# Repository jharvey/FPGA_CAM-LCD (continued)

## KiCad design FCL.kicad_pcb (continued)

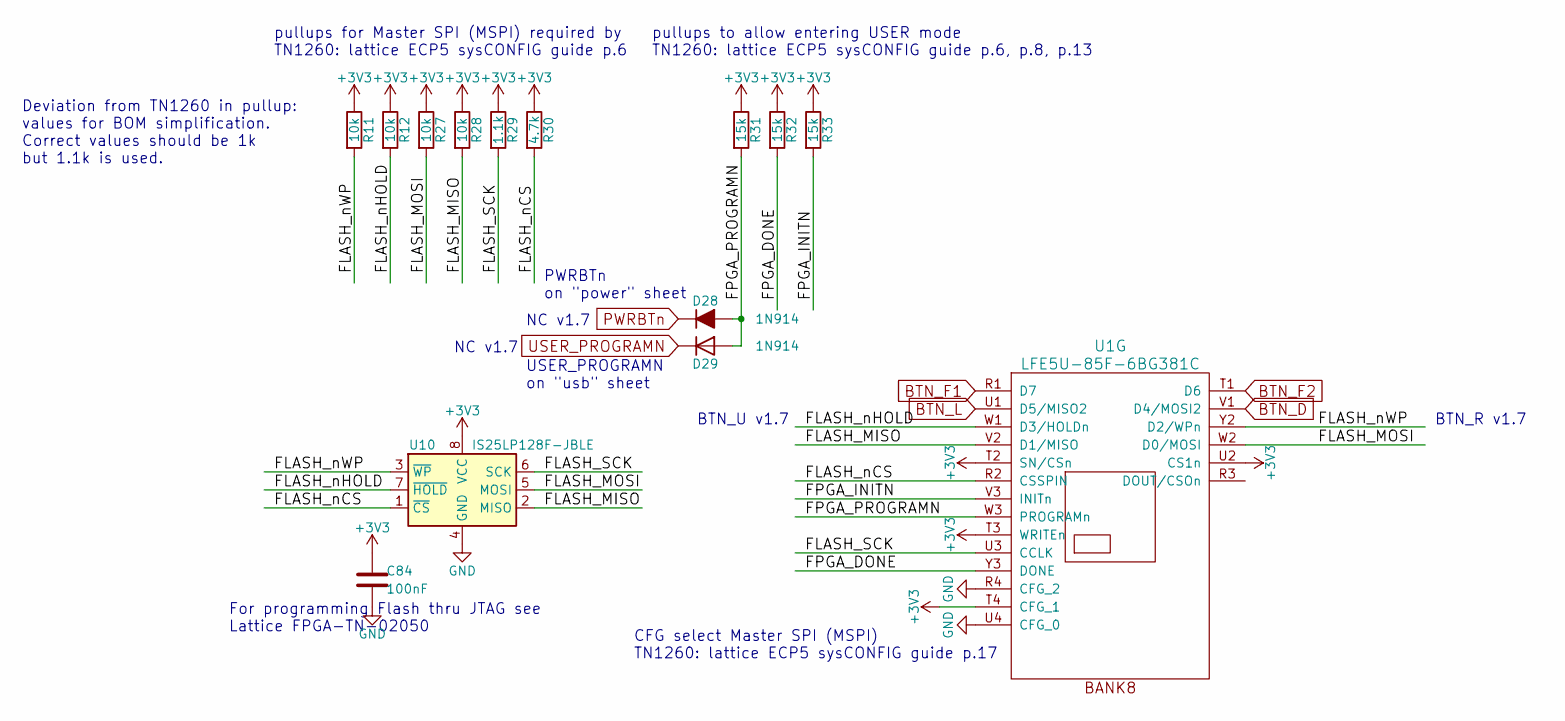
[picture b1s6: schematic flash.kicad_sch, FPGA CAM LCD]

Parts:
C84: 100nF; C_0402_1005Metric; LCSC C1525
D28: 1N914; D_SOD-323_HandSoldering; Digike_y 1N4148WXTPMSCT-ND
D29: 1N914; D_SOD-323_HandSoldering
R11: 10k; R_0603_1608Metric; MPN RC0603FR-0710KL; Mouser 603-RC0603FR-0710KL
R12, R27, R28: 10k; R_0603_1608Metric
R29: 1.1k; R_0603_1608Metric
R30: 4.7k; R_0603_1608Metric; MPN AC0603FR-104K7L
R31, R32, R33: 15k; R_0603_1608Metric
U1: LFE5U-85F-6BG381C; BGA-381_pitch0.8mm_dia0.4mm; MPN LFE5U-85F-6BG381C
U10: IS25LP128F-JBLE; SOA008-150-208mil; MPN IS25LP128F-JBLE; Mouser 454-W25Q128JVSIMTR

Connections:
+3V3: C84.1, R11.1, R12.1, R27.1, R28.1, R29.1, R30.1, R31.1, R32.1, R33.1, U1.T2 (SN/CSn), U1.T3 (WRITEn), U1.T4 (CFG_1), U1.U2 (CS1n), U10.8 (VCC); also elsewhere on the board
/flash/FLASH_MISO: R28.2, U1.V2 (D1/MISO), U10.2 (MISO)
/flash/FLASH_MOSI: R27.2, U1.W2 (D0/MOSI), U10.5 (MOSI)
/flash/FLASH_SCK: R29.2, U1.U3 (CCLK), U10.6 (SCK)
/flash/FLASH_nCS: R30.2, U1.R2 (CSSPIN), U10.1 (~CS)
/flash/FLASH_nHOLD: R12.2, U1.W1 (D3/HOLDn), U10.7 (~HOLD)
/flash/FLASH_nWP: R11.2, U1.Y2 (D2/WPn), U10.3 (~WP)
/flash/FPGA_DONE: R32.2, U1.Y3 (DONE)
/flash/FPGA_INITN: R33.2, U1.V3 (INITn)
/flash/FPGA_PROGRAMN: D28.2 (A), D29.2 (A), R31.2, U1.W3 (PROGRAMn)
BTN_D: U1.V1 (D4/MOSI2)
BTN_F1: U1.R1 (D7)
BTN_F2: U1.T1 (D6)
BTN_L: U1.U1 (D5/MISO2)
GND: C84.2, U1.R4 (CFG_2), U1.U4 (CFG_0), U10.4 (GND); also elsewhere on the board
PWRBTn: D28.1 (K); also elsewhere on the board
USER_PROGRAMN: D29.1 (K); also elsewhere on the board

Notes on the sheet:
CFG select Master SPI (MSPI) TN1260: lattice ECP5 sysCONFIG guide p.17
USER_PROGRAMN on "usb" sheet
NC v1.7
For programming Flash thru JTAG see Lattice FPGA-TN-02050
Deviation from TN1260 in pullup: values for BOM simplification. Correct values should be 1k but 1.1k is used.
BTN_R v1.7
pullups to allow entering USER mode TN1260: lattice ECP5 sysCONFIG guide p.6, p.8, p.13
PWRBTn on "power" sheet
BTN_U v1.7
pullups for Master SPI (MSPI) required by TN1260: lattice ECP5 sysCONFIG guide p.6

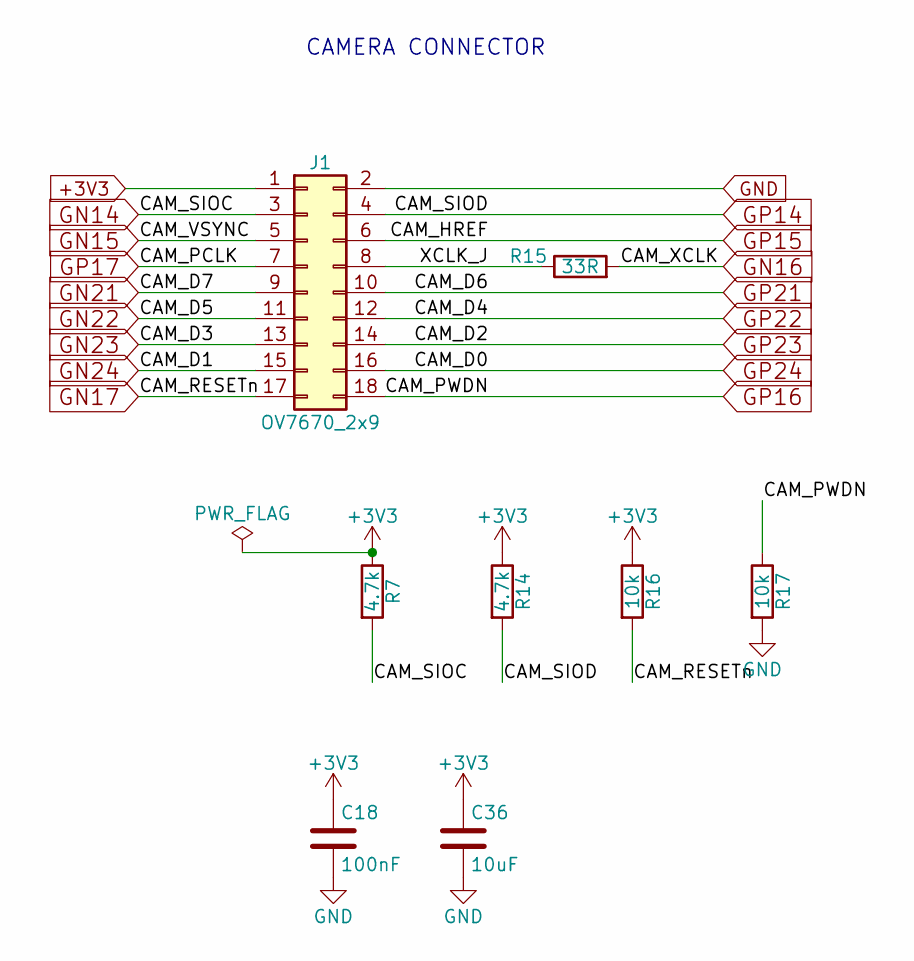
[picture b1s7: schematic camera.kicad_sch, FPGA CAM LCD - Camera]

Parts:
C18: 100nF; C_0402_1005Metric; LCSC C1525
C36: 10uF; C_0805_2012Metric; LCSC C15850
J1: OV7670_2x9; PinSocket_2x09_P2.54mm_Vertical; LCSC C71956
R7, R14: 4.7k; R_0402_1005Metric; LCSC C25900
R15: 33R; R_0402_1005Metric; LCSC C25105
R16, R17: 10k; R_0402_1005Metric; LCSC C25744

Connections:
+3V3: C18.1, C36.1, J1.1, R7.1, R14.1, R16.1; also elsewhere on the board
/camera/XCLK_J: J1.8, R15.1
CAM_XCLK: R15.2; also elsewhere on the board
GN14: J1.3, R7.2; also elsewhere on the board
GN15: J1.5; also elsewhere on the board
GN17: J1.17, R16.2; also elsewhere on the board
GN21: J1.9; also elsewhere on the board
GN22: J1.11; also elsewhere on the board
GN23: J1.13; also elsewhere on the board
GN24: J1.15; also elsewhere on the board
GND: C18.2, C36.2, J1.2, R17.2; also elsewhere on the board
GP14: J1.4, R14.2; also elsewhere on the board
GP15: J1.6; also elsewhere on the board
GP16: J1.18, R17.1; also elsewhere on the board
GP17: J1.7; also elsewhere on the board
GP21: J1.10; also elsewhere on the board
GP22: J1.12; also elsewhere on the board
GP23: J1.14; also elsewhere on the board
GP24: J1.16; also elsewhere on the board

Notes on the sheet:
CAMERA CONNECTOR

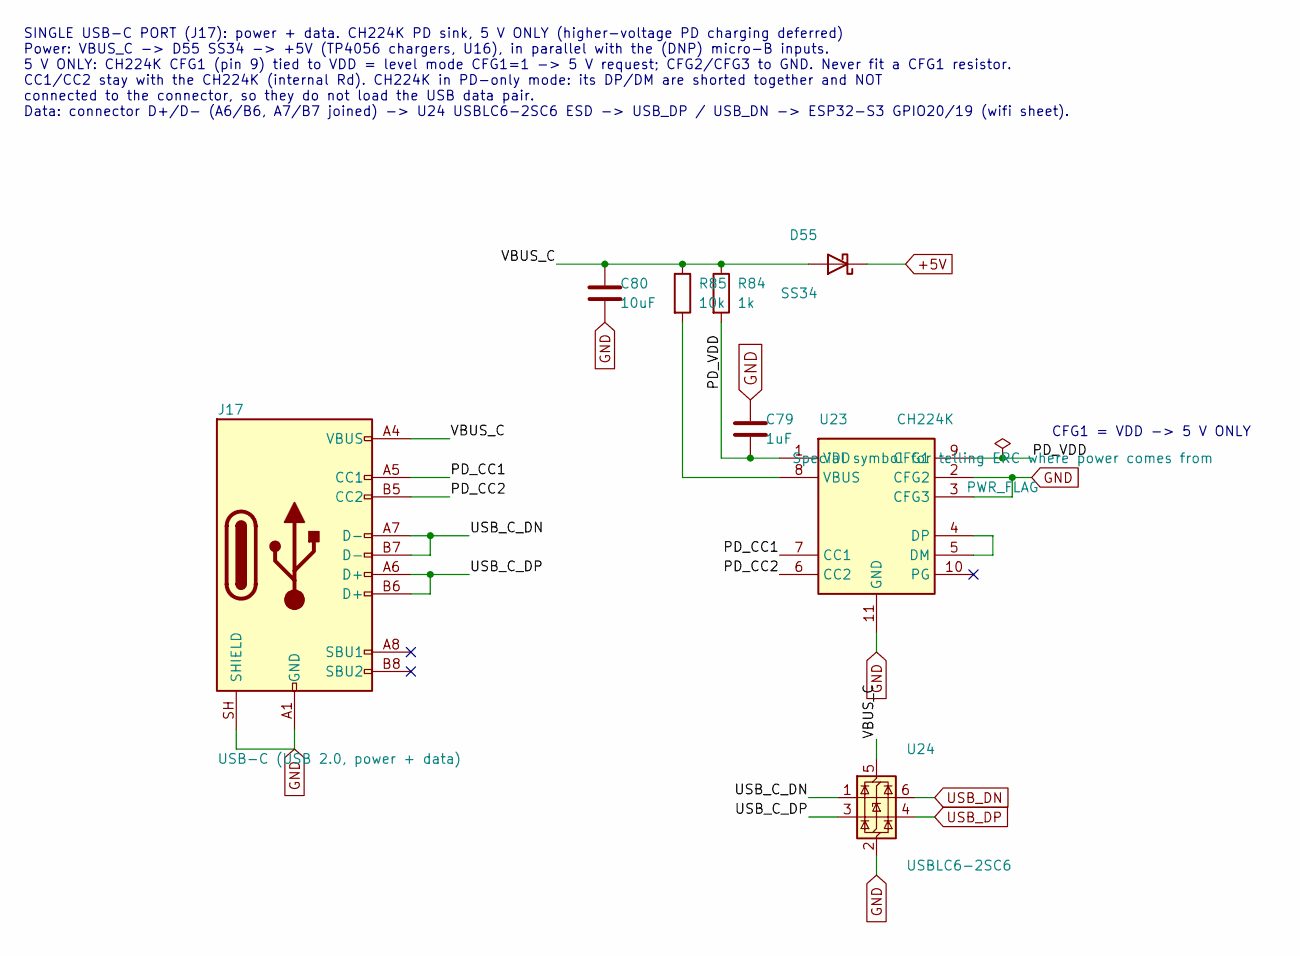
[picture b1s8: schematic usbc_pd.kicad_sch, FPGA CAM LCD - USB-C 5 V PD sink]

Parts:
C79: 1uF; C_0603_1608Metric; LCSC C15849
C80: 10uF; C_0805_2012Metric; LCSC C15850
D55: SS34; D_SMA; MPN SS34; LCSC C8678
J17: USB-C (USB 2.0, power + data); USB_C_Receptacle_HCTL_HC-TYPE-C-16P-01A; MPN HC-TYPE-C-16P-01A; LCSC C2894897
R84: 1k; R_0603_1608Metric; LCSC C21190
R85: 10k; R_0402_1005Metric; LCSC C25744
U23: CH224K; SSOP-10-1EP_3.9x4.9mm_P1mm_EP2.1x3.3mm; MPN CH224K; LCSC C970725
U24: USBLC6-2SC6; SOT-23-6; MPN USBLC6-2SC6; LCSC C7519

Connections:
+5V: D55.1 (K); also elsewhere on the board
/usbc_pd/PD_CC1: J17.A5 (CC1), U23.7 (CC1)
/usbc_pd/PD_CC2: J17.B5 (CC2), U23.6 (CC2)
/usbc_pd/PD_VDD: C79.2, R84.2, U23.1 (VDD), U23.9 (CFG1)
/usbc_pd/USB_C_DN: J17.A7 (D-), J17.B7 (D-), U24.1 (I/O1)
/usbc_pd/USB_C_DP: J17.A6 (D+), J17.B6 (D+), U24.3 (I/O2)
/usbc_pd/VBUS_C: C80.1, D55.2 (A), J17.A4 (VBUS), J17.A9 (VBUS), J17.B4 (VBUS), J17.B9 (VBUS), R84.1, R85.1, U24.5 (VBUS)
GND: C79.1, C80.2, J17.A1 (GND), J17.A12 (GND), J17.B1 (GND), J17.B12 (GND), J17.SH (SHIELD), U23.2 (CFG2), U23.3 (CFG3), U23.11 (GND), U24.2 (GND); also elsewhere on the board
unnamed: U23.4 (DP), U23.5 (DM)
unnamed: R85.2, U23.8 (VBUS)
USB_DN: U24.6 (I/O1); also elsewhere on the board
USB_DP: U24.4 (I/O2); also elsewhere on the board

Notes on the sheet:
CFG1 = VDD -> 5 V ONLY
SINGLE USB-C PORT (J17): power + data. CH224K PD sink, 5 V ONLY (higher-voltage PD charging deferred) Power: VBUS_C -> D55 SS34 -> +5V (TP4056 chargers, U16), in parallel with the (DNP) micro-B inputs. 5 V ONLY: CH224K CFG1 (pin 9) tied to VDD = level mode CFG1=1 -> 5 V request; CFG2/CFG3 to GND. N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

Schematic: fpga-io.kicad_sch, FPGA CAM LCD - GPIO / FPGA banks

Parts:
B1, B2: PTS645; SW_SPST_PTS645Sx43SMTR92; MPN PTS645SL50SMTR92 LFS; Mouser 611-PTS645SL50SMTR92
D51, D52: 0; D_SMA_Jumper_NC; not fitted
D53, D54: RED; LED_0603_1608Metric; LCSC C2286
J2, J6: CONN_02X20; PinSocket_2x20_P2.54mm_Horizontal; not fitted
R67, R68: 10k; R_0402_1005Metric; LCSC C25744
R69, R70: 1k; R_0603_1608Metric; LCSC C21190
R74, R75: 4.7k; R_0402_1005Metric; LCSC C25900
U1: LFE5U-85F-6BG381C; BGA-381_pitch0.8mm_dia0.4mm; MPN LFE5U-85F-6BG381C

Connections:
+3V3: R67.1, R68.1, R74.1, R75.1; also elsewhere on the board
ADC_CNV: U1.B1 (PL35B); also elsewhere on the board
ADC_DIN: U1.C1 (PL38A); also elsewhere on the board
ADC_SCK: U1.D1 (PL38B); also elsewhere on the board
ADC_SDO: U1.E1 (PL38D); also elsewhere on the board
BTN1n: B1.2, R67.2, U1.E8 (PT13A)
BTN2n: B2.2, R68.2, U1.D8 (PT13B)
BTN_PWRn: U1.D6 (PT6B); also elsewhere on the board
CAM_XCLK: J6.9, U1.A18 (PT119A); also elsewhere on the board
FPDI_SCL: R74.2, U1.E12 (GR_PCLK1_1); also elsewhere on the board
FPDI_SDA: R75.2, U1.C15 (PT105B); also elsewhere on the board
GN0: J2.5, U1.A2 (PL35A); also elsewhere on the board
GN1: J2.7, U1.B3 (PL14D); also elsewhere on the board
GN2: J2.9, U1.C4 (PL14A); also elsewhere on the board
GN3: J2.11, U1.A4 (PL11A); also elsewhere on the board
GN4: J2.13, U1.B5 (PL11C); also elsewhere on the board
GN5: J2.15, U1.C6 (PT11A); also elsewhere on the board
GN6: J2.17, U1.A6 (PT4A); also elsewhere on the board
GN7: J2.23, U1.A7 (PT18A); also elsewhere on the board
GN8: J2.25, U1.B8 (PT15B); also elsewhere on the board
GN9: J2.27, U1.C9 (PT54A); also elsewhere on the board
GN10: J2.29, U1.A9 (GR_PCLK0_1); also elsewhere on the board
GN11: J2.31, U1.B10 (GR_PCLK0_0); also elsewhere on the board
GN12: J2.33, U1.C11 (PCLKC0_0); also elsewhere on the board
GN13: J2.35, U1.A11 (PCLKC0_1); also elsewhere on the board
GN14: J6.5, U1.B20 (PT121B); also elsewhere on the board
GN15: J6.7, U1.A19 (PT121A); also elsewhere on the board
GN17: J6.11, U1.A12 (PT76A); also elsewhere on the board
GN21: J6.23, U1.A17 (PT116A); also elsewhere on the board
GN22: J6.25, U1.B16 (PT110B); also elsewhere on the board
GN23: J6.27, U1.B15 (PT105A); also elsewhere on the board
GN24: J6.29, U1.A14 (PT83A); also elsewhere on the board
GND: B1.1, B2.1, D53.1 (K), D54.1 (K), U1.T6 (VCCA0), U1.T7 (VCCHTX0_D0CH0), U1.T8 (VCCHRX0_D0CH0), U1.T9 (VCCHRX0_D0CH1), U1.T10 (VCCHTX0_D0CH1), U1.T11 (VCCHTX0_D1CH0), U1.T12 (VCCHRX0_D1CH0), U1.T13 (VCCHRX0_D1CH1), U1.T14 (VCCHTX0_D1CH1), U1.T15 (VCCA1), U1.U6 (VCCA0), U1.U15 (VCCA1), U1.V10 (VCCAUXA0), U1.V11 (VCCAUXA0), U1.V17 (VCCAUXA1), U1.V18 (VCCAUXA1), U1.W20 (REFCLKN_D1), U1.Y5 (HDRXP0_D0CH0), U1.Y6 (HDRXN0_D0CH0), U1.Y7 (HDRXP0_D0CH1), U1.Y8 (HDRXN0_D0CH1), U1.Y11 (REFCLKP_D0), U1.Y12 (REFCLKN_D0), U1.Y14 (HDRXP0_D1CH0), U1.Y15 (HDRXN0_D1CH0), U1.Y16 (HDRXP0_D1CH1), U1.Y17 (HDRXN0_D1CH1), U1.Y19 (REFCLKP_D1); also elsewhere on the board
GP0: J2.6, U1.C3 (PL17C); also elsewhere on the board
GP1: J2.8, U1.A3 (PL14C); also elsewhere on the board
GP2: J2.10, U1.B4 (PL14B); also elsewhere on the board
GP3: J2.12, U1.C5 (PL11D); also elsewhere on the board
GP4: J2.14, U1.A5 (PL11B); also elsewhere on the board
GP5: J2.16, U1.B6 (PT4B); also elsewhere on the board
GP6: J2.18, U1.C7 (PT11B); also elsewhere on the board
GP7: J2.24, U1.C8 (PT15A); also elsewhere on the board
GP8: J2.26, U1.A8 (PT18B); also elsewhere on the board
GP9: J2.28, U1.B9 (PT58A); also elsewhere on the board
GP10: J2.30, U1.C10 (PT58B); also elsewhere on the board
GP11: J2.32, U1.A10 (PCLKT0_1); also elsewhere on the board
GP12: J2.34, U1.B11 (PCLKT0_0); also elsewhere on the board
GP13: J2.36, U1.H4 (GR_PCLK7_1); also elsewhere on the board
GP14: J6.6, U1.B19 (PT119B); also elsewhere on the board
GP15: J6.8, U1.B18 (PT116B); also elsewhere on the board
GP16: J6.10, U1.B13 (PT78A); also elsewhere on the board
GP17: J6.12, U1.B12 (PCLKT1_0); also elsewhere on the board
GP21: J6.24, U1.B17 (PT114A); also elsewhere on the board
GP22: J6.26, U1.A16 (PT110A); also elsewhere on the board
GP23: J6.28, U1.A15 (PT103A); also elsewhere on the board
GP24: J6.30, U1.A13 (PT76B); also elsewhere on the board
IMU_INT2: U1.E3 (PL20B); also elsewhere on the board
LED0: R69.1, U1.B2 (VREF1_7)
LED1: R70.1, U1.C2 (PL35D)
unnamed: D51.1, D52.2
unnamed: D51.2, J6.39
unnamed: D52.1, J6.40
unnamed: D53.2 (A), R69.2
unnamed: D54.2 (A), R70.2
unnamed: J2.1, J2.2, J2.19, J2.20, J2.39, J2.40
unnamed: J2.3, J2.4, J2.21, J2.22, J2.37, J2.38, J6.3, J6.4, J6.21, J6.22, J6.37, J6.38
unnamed: J6.1, J6.2, J6.19, J6.20
SRV_PWM2: U1.D15 (PT107A); also elsewhere on the board
SRV_PWM3: U1.D13 (PT80A); also elsewhere on the board
SRV_PWM4: U1.D16 (PT112B); also elsewhere on the board
SRV_PWM5: U1.D14 (PT85A); also elsewhere on the board

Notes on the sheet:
STPS2L40AF
J1 J2 PIN numbering 1-40 is for FEMALE 90° ANGLED header. For MALE VERTICAL header, SWAP EVEN and ODD pin numbers.
PCLKC0_1
NC v1.7
U1 unit H - SERDES balls. Fitted part is LFE5U-85F (no SERDES): per ECP5U-85 pinout (CABGA381) these balls are GND (tie to GND), HDTX balls are RESERVED (leave unconnected).
PCLKC0_0
GR_PCLK0_1
PCLKC7_1
DAC WIFI_GPIO26
PCLKT0_0
GR_PCLK3_0
GP,GN 0-7 single-ended connected to BANK0 GP,GN 8-13 differential bidirectional connected to BANK7
GPIO route only A/B pairs as those are differential bidirectional don't route C/D pairs to GPIO as those can be differential input only BANK0,1 are single-ended (non-differential)
GP,GN 14-21 differential bidirectional connected to BANK2,3 on "ram" sheet GP,GN 22-27 single-ended connected to BANK1 on "gpdi" sheet
GR_PCLK7_1
RTC (U7, power sheet) I2C pull-ups
DAC WIFI_GPIO25
PCLKT7_1
NC <v3.1.2
GR_PCLK0_0
PCLKT0_1
SINGLE ENDED - NOT DIFFERENTIAL
USER I/O (monocular) B1/B2: active-low buttons, 10k pull-ups, debounce in FPGA D53/D54: active-high status LEDs (LED0 = configured/heartbeat, LED1 = user)

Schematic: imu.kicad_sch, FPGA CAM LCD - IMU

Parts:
C76, C87, C89: 100nF; C_0402_1005Metric; LCSC C1525
C77: 2.2uF; C_0805_2012Metric; LCSC C87995
C78: 10nF; C_0402_1005Metric; LCSC C15195
C86: 220nF; C_0603_1608Metric; LCSC C326805
C88: 10uF; C_0805_2012Metric; LCSC C15850
R76, R77: 4.7k; R_0402_1005Metric; LCSC C25900
U22: ICM-42688-P; LGA-14_3x2.5mm_P0.5mm_LayoutBorder3x4y; MPN ICM-42688-P; LCSC C1850418
U25: LIS2MDL; LGA-12_2x2mm_P0.5mm; LCSC C919695

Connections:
+3V3: C76.1, C77.1, C78.1, C87.1, C88.1, C89.1, R76.1, R77.2, U22.5 (VDDIO), U22.8 (VDD), U22.12 (AP_CS), U25.3 (~CS), U25.9 (Vdd), U25.10 (Vdd_IO); also elsewhere on the board
/imu/MAG_C1: C86.1, U25.5 (C1)
GND: C76.2, C77.2, C78.2, C86.2, C87.2, C88.2, C89.2, U22.1 (AP_AD0/AP_SDO), U22.6 (GND), U22.7 (RESV_GND), U25.6 (GND), U25.8 (GND); also elsewhere on the board
IMU_INT1: U22.4 (INT1); also elsewhere on the board
IMU_INT2: U22.9 (INT2/FSYNC/CLKIN); also elsewhere on the board
IMU_SCL: R76.2, U22.13 (AP_SCL/AP_SCLK), U25.1 (SCL/SPC); also elsewhere on the board
IMU_SDA: R77.1, U22.14 (AP_SDA/AP_SDIO), U25.4 (SDA/SDI/SDO); also elsewhere on the board
MAG_DRDY: U25.7 (DRDY); also elsewhere on the board

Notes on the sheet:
IMU - TDK InvenSense ICM-42688-P (LCSC C1850418, JLCPCB extended part) I2C mode: AP_CS = VDDIO, address 0x68 (AP_AD0 = GND). Bus to FPGA: IMU_SCL P16, IMU_SDA K17, IMU_INT1 K16, IMU_INT2 E3 (pin 9 can be INT2 or FSYNC input, e.g. camera frame sync from FPGA). Decoupling per DS-000347 Table 10: VDD 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
Magnetometer (compass) - ST LIS2MDL, LCSC C919695 (JLCPCB extended part) I2C address 0x1E on the IMU bus (IMU_SCL/IMU_SDA, pull-ups R76/R77). CS tied high = I2C. DRDY -> FPGA ball L17 (MAG_DRDY). C86 220 nF low-ESR right at pins 5/6 (C1 pulse current). C87 100 nF + C88 10 uF at pin 9 (Vdd), C89 100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

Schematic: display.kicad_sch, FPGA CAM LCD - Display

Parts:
C37: 10uF; C_0805_2012Metric; MPN CL21A106KAYNNNE; LCSC C15850
C38: 4.7uF 50V; C_1206_3216Metric; MPN 1206B475K500NT; LCSC C29823
C74: 100nF; C_0402_1005Metric; LCSC C1525
C75: 10uF; C_0805_2012Metric; LCSC C15850
D1: SS14; D_SMA; MPN SS14; LCSC C2480
J7: NHD-2.1-480480AF-ASXP; Hirose_FH12-40S-0.5SH_1x40-1MP_P0.50mm_Horizontal; LCSC C202114
L4: 4.7uH; L_Sunlord_SWPA3015S; MPN SWPA3015S4R7MT; LCSC C19398
R18: 100k; R_0402_1005Metric; LCSC C25741
R19: 2R0; R_0603_1608Metric; MPN 0603WAF200KT5E; LCSC C22977
U8: AP3032KTR-G1; SOT-23-6; MPN AP3032KTR-G1; LCSC C264086

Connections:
+3V3: C74.1, C75.1, J7.3, J7.38; also elsewhere on the board
/display/LCD_BL_A: C38.1, D1.1 (K), J7.2, U8.5 (V_{OUT})
/display/LCD_BL_K: J7.1, R19.1, U8.3 (FB)
/display/LCD_BL_SW: D1.2 (A), L4.1, U8.1 (SW)
GN0: J7.11; also elsewhere on the board
GN1: J7.13; also elsewhere on the board
GN2: J7.15; also elsewhere on the board
GN3: J7.17; also elsewhere on the board
GN4: J7.19; also elsewhere on the board
GN5: J7.21; also elsewhere on the board
GN6: J7.23; also elsewhere on the board
GN7: J7.25; also elsewhere on the board
GN8: J7.27; also elsewhere on the board
GN9: J7.29; also elsewhere on the board
GN10: J7.31; also elsewhere on the board
GN11: J7.33; also elsewhere on the board
GN12: J7.35; also elsewhere on the board
GN13: J7.37; also elsewhere on the board
GND: C37.2, C38.2, C74.2, C75.2, J7.4, J7.7, J7.10, J7.39, J7.40, J7.MP (MountPin), R18.2, R19.2, U8.2 (GND); also elsewhere on the board
GP0: J7.12; also elsewhere on the board
GP1: J7.14; also elsewhere on the board
GP2: J7.16; also elsewhere on the board
GP3: J7.18; also elsewhere on the board
GP4: J7.20; also elsewhere on the board
GP5: J7.22; also elsewhere on the board
GP6: J7.24; also elsewhere on the board
GP7: J7.26; also elsewhere on the board
GP8: J7.28; also elsewhere on the board
GP9: J7.30; also elsewhere on the board
GP10: J7.32; also elsewhere on the board
GP11: J7.34; also elsewhere on the board
GP12: J7.36; also elsewhere on the board
GP13: R18.1, U8.4 (CTRL); also elsewhere on the board
VSYS: C37.1, L4.2, U8.6 (V_{IN}); also elsewhere on the board

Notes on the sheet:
LCD CONNECTOR.

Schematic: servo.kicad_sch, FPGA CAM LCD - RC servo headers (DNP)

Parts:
J_SRV1, J_SRV2, J_SRV3, J_SRV4, J_SRV5, J_SRV6: RC_SERVO; PinHeader_1x03_P2.54mm_Vertical; not fitted
R78, R79, R80, R81, R82, R83: 1k; R_0603_1608Metric; LCSC C21190; not fitted

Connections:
GND: J_SRV1.3, J_SRV2.3, J_SRV3.3, J_SRV4.3, J_SRV5.3, J_SRV6.3; also elsewhere on the board
unnamed: J_SRV1.1, R78.2
unnamed: J_SRV2.1, R79.2
unnamed: J_SRV3.1, R80.2
unnamed: J_SRV4.1, R81.2
unnamed: J_SRV5.1, R82.2
unnamed: J_SRV6.1, R83.2
SERVO_V: J_SRV1.2, J_SRV2.2, J_SRV3.2, J_SRV4.2, J_SRV5.2, J_SRV6.2
SRV_PWM1: R78.1; also elsewhere on the board
SRV_PWM2: R79.1; also elsewhere on the board
SRV_PWM3: R80.1; also elsewhere on the board
SRV_PWM4: R81.1; also elsewhere on the board
SRV_PWM5: R82.1; also elsewhere on the board
SRV_PWM6: R83.1; also elsewhere on the board

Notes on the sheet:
RC SERVO HEADERS - 6x 1x3 2.54 mm, ALL DNP FOR THE FIRST PROTOTYPE Pinout (standard RC servo): 1 = Signal (1-2 ms pulse, 3.3 V from FPGA via 1k), 2 = SERVO_V (+V), 3 = GND SERVO_V power source NOT decided yet: later jumper to VSYS or feed from a dedicated regulator (servo stall current can exceed 1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

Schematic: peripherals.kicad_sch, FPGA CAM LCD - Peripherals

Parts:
C90, C91, C92, C94, C95: 100nF; C_0402_1005Metric; LCSC C1525
C93: 4.7uF; C_0603_1608Metric; LCSC C19666
C96: 10uF; C_0805_2012Metric; LCSC C15850
J8: Speaker; JST_SH_BM02B-SRSS-TB_1x02-1MP_P1.00mm_Vertical; LCSC C160388
MK1: ICS-43434; InvenSense_ICS-43434-6_3.5x2.65mm; LCSC C5656610
R87: 100k; R_0402_1005Metric; LCSC C25741
R88, R89: 10k; R_0402_1005Metric; LCSC C25744
TP1, TP2: GND; TestPoint_Pad_D1.0mm
TP3: +3V3; TestPoint_Pad_D1.0mm
TP4: +1V1; TestPoint_Pad_D1.0mm
TP5: +2V5; TestPoint_Pad_D1.0mm
TP6: VSYS; TestPoint_Pad_D1.0mm
TP7: +5V; TestPoint_Pad_D1.0mm
TP8: IMU_SCL; TestPoint_Pad_D1.0mm
TP9: IMU_SDA; TestPoint_Pad_D1.0mm
TP10: FPDI_SCL; TestPoint_Pad_D1.0mm
TP11: FPDI_SDA; TestPoint_Pad_D1.0mm
TP12: WIFI_TXD; TestPoint_Pad_D1.0mm
TP13: WIFI_RXD; TestPoint_Pad_D1.0mm
U26: LPS22DF; ST_HLGA-10_2x2mm_P0.5mm_LayoutBorder3x2y; LCSC C3253714
U27: VL53L1CXV0FY/1; ST_VL53L1x; LCSC C190004
U28: MAX98357A; TQFN-16-1EP_3x3mm_P0.5mm_EP1.23x1.23mm; LCSC C910544

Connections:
+1V1: TP4.1; also elsewhere on the board
+2V5: TP5.1; also elsewhere on the board
+3V3: C90.1, C91.1, C92.1, C93.1, C94.1, MK1.5 (VDD), R88.1, R89.1, TP3.1, U26.1 (Vdd_IO), U26.6 (~CS), U26.10 (VDD), U27.1 (AVDDVCSEL), U27.11 (AVDD); also elsewhere on the board
+5V: TP7.1; also elsewhere on the board
/peripherals/SPK_N: J8.2, U28.10 (OUTN)
/peripherals/SPK_P: J8.1, U28.9 (OUTP)
AMP_SD: R87.1, U28.4 (~SD_MODE); also elsewhere on the board
BARO_INT: U26.7 (INT_DRDY); also elsewhere on the board
FPDI_SCL: TP10.1; also elsewhere on the board
FPDI_SDA: TP11.1; also elsewhere on the board
GND: C90.2, C91.2, C92.2, C93.2, C94.2, C95.2, C96.2, MK1.2 (LR), MK1.3 (GND), R87.2, TP1.1, TP2.1, U26.3 (GND), U26.5 (SA0), U26.8 (GND_IO), U26.9 (GND), U27.2 (AVSSVCSEL), U27.3 (GND), U27.4 (GND), U27.6 (GND), U27.12 (GND), U28.3 (GND), U28.11 (GND), U28.15 (GND), U28.17 (PAD); also elsewhere on the board
I2S_BCLK: MK1.4 (SCK), U28.16 (BCLK); also elsewhere on the board
I2S_MIC: MK1.6 (SD); also elsewhere on the board
I2S_SPK: U28.1 (DIN); also elsewhere on the board
I2S_WS: MK1.1 (WS), U28.14 (LRCLK); also elsewhere on the board
IMU_SCL: TP8.1, U26.2 (SCL), U27.10 (SCL); also elsewhere on the board
IMU_SDA: TP9.1, U26.4 (SDA), U27.9 (SDA); also elsewhere on the board
TOF_INT: R89.2, U27.7 (GPIO1); also elsewhere on the board
TOF_XSHUT: R88.2, U27.5 (XSHUT); also elsewhere on the board
VSYS: C95.1, C96.1, TP6.1, U28.7 (VDD), U28.8 (VDD); also elsewhere on the board
WIFI_RXD: TP13.1; also elsewhere on the board
WIFI_TXD: TP12.1; also elsewhere on the board

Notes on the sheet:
Barometer - ST LPS22DF (LCSC C3253714), I2C address 0x5C (SA0 = GND), CS high = I2C. On the IMU bus (pull-ups R76/R77 on the imu sheet). INT_DRDY -> FPGA ball M17 (BARO_INT). C90 100 nF at VDD (pin 10), C91 100 nF at Vdd_IO (pin 1). Keep the vent hole clear; no conformal coat.
Distance sensor - ST VL53L1X (LCSC C190004), time-of-flight up to 4 m, I2C address 0x29 (default). On the IMU bus. XSHUT <- FPGA N16 (TOF_XSHUT, R88 10k pull-up = on), GPIO1 -> FPGA N17 (TOF_INT, R89 10k pull-up). C92 100 nF + C93 4.7 uF at AVDD/AVDDVCSEL (pins 11/1). Mount at a board edge looking 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
Microphone - TDK ICS-43434 (LCSC C5656610), I2S, bottom port: needs a ~0.8 mm hole through the PCB under the port and an opening in the case. L/R = GND -> left slot. Shares BCLK/WS with the amplifier (ESP32-S3 I2S0, full duplex). ESP32: I2S_BCLK GPIO35, I2S_WS GPIO36, I2S_SPK GPIO37 (out), I2S_MIC 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
Speaker amplifier - Maxim MAX98357A (LCSC C910544), I2S in, class-D BTL out to J8 (4-8 ohm speaker, no output filter needed for short leads). VDD = VSYS (3.0-4.2 V). GAIN_SLOT open = 9 dB. SD_MODE <- ESP32 GPIO47 (AMP_SD): high = on, left channel; R87 100k keeps the amp off while the ESP32 boots. C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
Test points TP1-TP13: 1.0 mm round SMD pads (not in BOM). Ground, rails, both I2C buses and the ESP32-FPGA UART. JTAG is on J4 (TC2030).

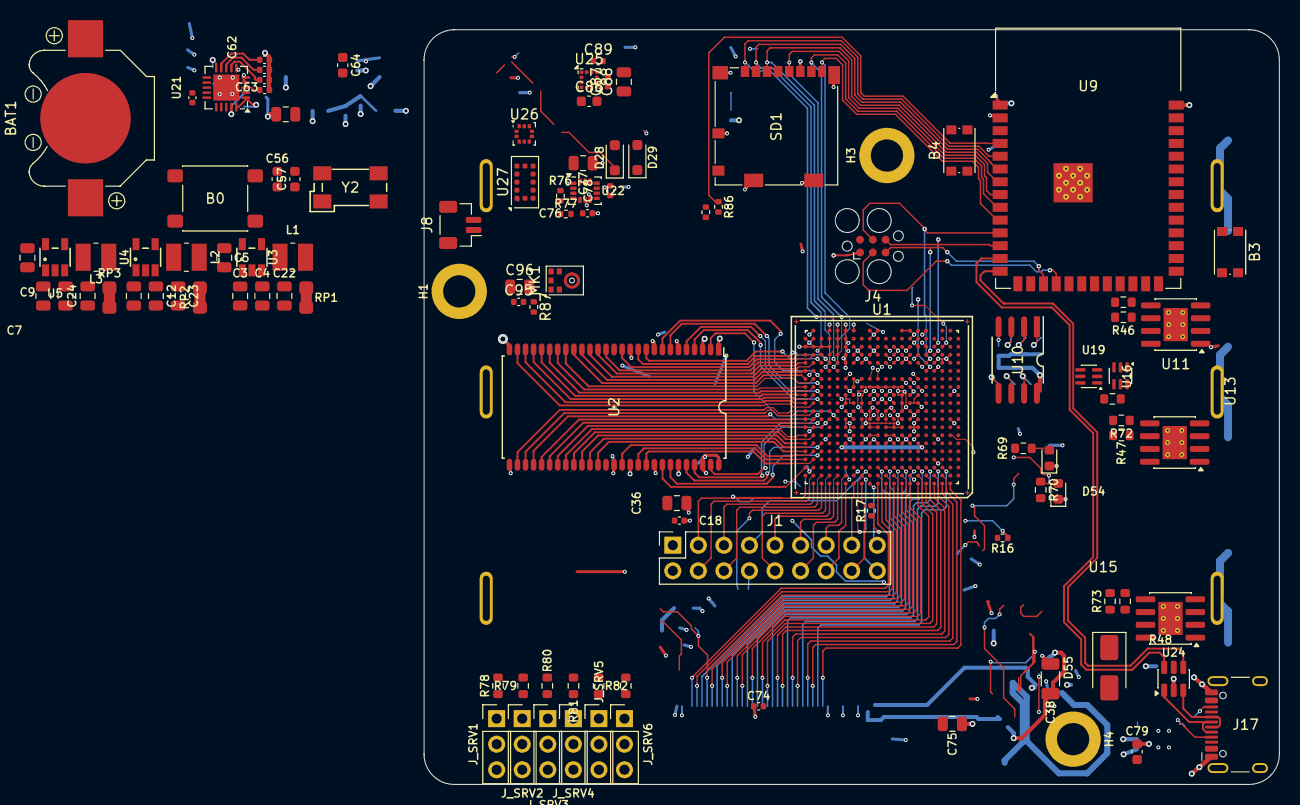
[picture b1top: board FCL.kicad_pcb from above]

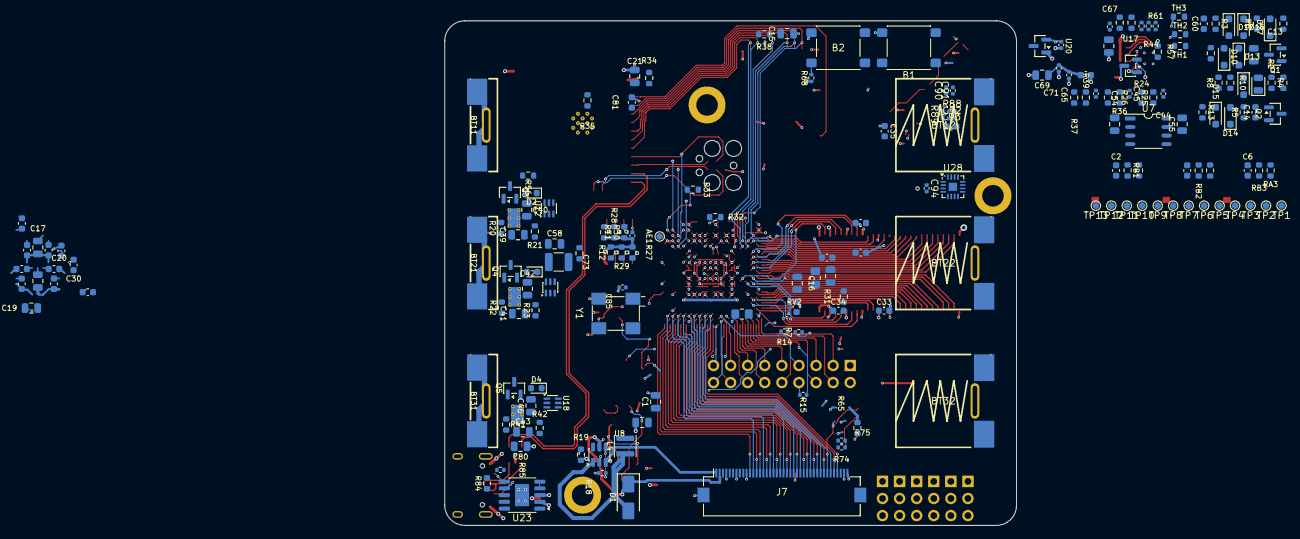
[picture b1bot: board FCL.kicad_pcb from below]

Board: 4 copper layers, 85.0 x 75.0 mm, 285 parts (179 on the bottom side), 239 nets.
